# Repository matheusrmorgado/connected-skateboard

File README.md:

# Módulo eletrônico para monitoramento de skates

## Plataforma de visualização de dados

> https://skate-do-futuro-mrm.web.app

## Referências

#### Sensoriamento e Controle Realtime com Firebase e ESP8266

> https://medium.com/@alvaroviebrantz/sensoriamento-realtime-com-firebase-e-esp8266-6e54b9bff1c1

#### ESP8266 – Manipular Modelo 3D con MPU6050 (PHP + WebGL + Three.js)

> http://www.sinaptec.alomar.com.ar/2017/10/proyecto-3-esp8266-manipular-modelo-3d.html

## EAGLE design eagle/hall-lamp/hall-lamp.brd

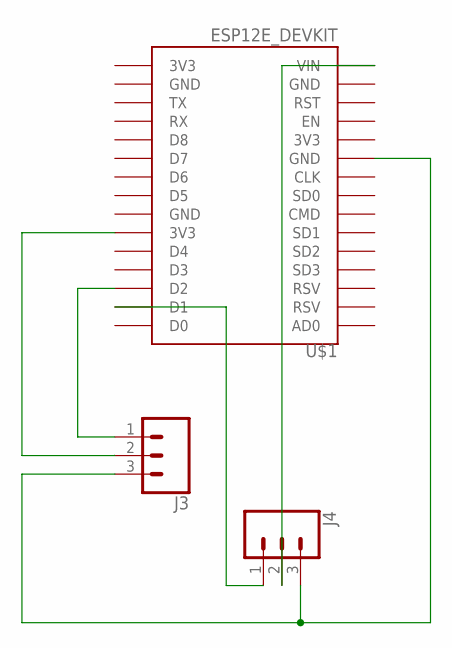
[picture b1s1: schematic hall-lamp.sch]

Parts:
J3, J4: CONN_03; 1X03
U$1: ESP12E_DEVKIT

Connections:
unnamed: J3.3, J4.3, U$1.GND@0 (GND)
unnamed: J3.1, U$1.D2
unnamed: J3.2, U$1.3V3@1 (3V3)
unnamed: J4.1, U$1.D1
unnamed: J4.2, U$1.VIN

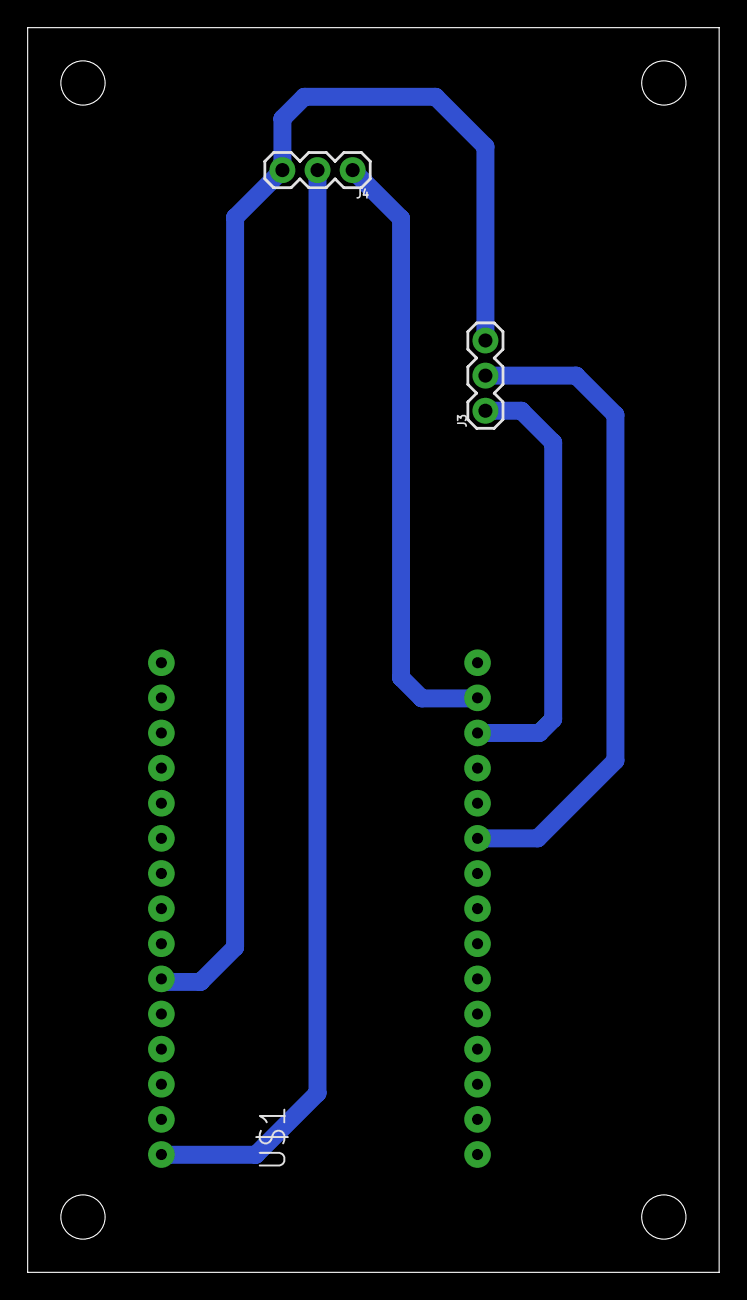
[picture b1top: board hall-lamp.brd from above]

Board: 2 copper layers, 50.0 x 90.0 mm, 3 parts (0 on the bottom side), 5 nets.

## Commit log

2019-06-30 Update project files
2019-06-30 Update project documentation

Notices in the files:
parts and their libraries:
SparkFun-Connectors: Licensing: Creative Commons ShareAlike 4.0 International - https://creativecommons.org/licenses/by-sa/4.0
